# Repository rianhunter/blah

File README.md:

# [CXADC][cxadc] clock generator and audio ADC

A project to synchronously clock two (or more) [CXADC][cxadc] PCIe cards and an extra audio ADC from an external clock generator, for [VHS-Decode][vhs-decode] setups.
This enables sync capturing of the two RF streams (RF Video and RF HiFi audio from a VHS), in addition to a stereo audio stream (linear VHS audio).

The above picture shows the mainboard, which you would typically mount inside your capture PC, along side the 2 CXADC cards.
The below diagram shows how a typical VHS capture is setup using the clock generator + audio ADC (this project).

The project consists of 3 main components:
- A PCB adapter that is installed per PCIe card.
  It contains only a couple of passive components per [cx25800-11z data sheet][google-cx25800-datasheet].
- The main PCB that combines a [Raspberry Pi Pico][pi-pico], with an [Adafruit Si5351A Clock Generator Breakout Board][si5351-adafruit], and a [PCM1802 board][pcm1802-product].
- The firmware for the [Raspberry Pi Pico][pi-pico], that implements a USB sound card and also controls the [Si5351A][si5351-adafruit] clock generator.
  The firmware is available pre-build and can be flashed to the [Raspberry Pi Pico][pi-pico] without additional tools.

## Why you would need this

To capture VHS conveniently and then decode it with the amazing [VHS-Decode][vhs-decode], you need two [CXADC][cxadc] PCIe cards and an additional audio ADC.
One [CXADC][cxadc] card will capture the RF video stream at usually 20MSPS 10bit.
The other [CXADC][cxadc] card will capture RF HiFi audio at usually 10MSPS 8bit.
The additional audio ADC captures the linear audio track from the VHS.
So you have 3 independent pieces of hardware that each captures a part of the VHS tapes content.

Each of the 3 pieces has its own quartz oscillator, to drive its logic.
[CXADC][cxadc] PCIe cards usually come with a 28.6MHz quartz, that is commonly replaced with a 40MHz one for better performance.
The additional linear audio stream could be captured with an additional USB audio interface, which of course has its own quartz.

As every real device, quartzes have tolerances, resulting in frequency errors.
E.g. a 40MHz quartz might actually be 40.000005MHz or 39.999995MHz.
This error is due to manufacturing tolerance and basically random.
So each of the 3 quartzes will be slightly different, and you can't really know by how much.
If you just capture from one of these sources, then this tiny error does not matter.
But if you capture 3 streams that all come from the same source, a VHS tape, then it does!

So lets say that one [CXADC][cxadc] card is slightly faster than the other, because its quartz runs a bit faster than the others.
When you've finished your capture from both cards, one file will contain slightly more samples than came from the other stream.
This means the signal / information in both files is actually not aligned with each other any more, like it used to be on the VHS tape.
To align them again, you have to do (manual) post processing to find out how much they differ, and then *resample* one of them to fit the other.
The same goes for the linear audio as well, there may now be slightly more or less samples in your recorded wav file than expected.

This project solves all of this by replacing the quartz crystals on [CXADC][cxadc] PCIe cards with the output from a clock generator.
The clock generator produces the clocks for both cards from a single source (also a quartz).
This single source of course has a slight error, but as both [CXADC][cxadc] cards are now fed from the *same* source, both are now always in sync!
To also cover the linear audio capturing / recording, the project includes a [PCM1802 ADC][pcm1802-product].
This extra audio ADC is also synchronously clocked from the same clock generator, so it is also always in sync to the two [CXADC][cxadc] cards.

As an added bonus, the clock generator is programmable, so the output sample rates for the [CXADC][cxadc] cards can be changed!
This can be configured during system runtime, via the same USB audio interface that also streams the [PCM1802 ADC][pcm1802-product] samples.
And as one more feature, it also contains an additional digital input, that can be connected to the head switch signal of your VHS player.
This signal will be recorded along side the linear audio, enabling even more automation to sync up all those streams.

The above shows a 3ch recording as captured from the clock generator, a sine wave on the left, silence on the right, and a head-switch signal on the 3rd channel.
Read on to get all the details and find out how to build one yourself.

## Building one yourself

The build and installation guide can be found [over here][build-guide].
Have a look in the [mechanical section too](mechanical) for some (optional) 3D printable parts.
And once you built it, check out the [scripts][scripts] folder which holds some useful tools an examples around using this project.

## System overview and architecture

So you want to contribute, or just understand how it all works, then read on!
Lets start with a logical block diagram of the system.

The brain of the system is a [Raspberry Pi Pico][pi-pico] that implements a [USB UAC][wiki-usb-uac] device (aka a usb sound card).
The [USB UAC][wiki-usb-uac] device can be used to stream the captured samples from the [PCM1802][pcm1802-product] as a regular sound source.
In addition to audio streaming it also offers control over the sample rates for the ADC and [CXADC][cxadc] cards.
[USB UAC][wiki-usb-uac] is supported by all major OS and should work without the need for any additional drivers.
Here's the output from `arecord` when the clock gen is plugged in:

NOTE the following talks a lot about the implementation as a [USB UAC 2.0 audio device][wiki-usb-uac].
The backgrounds and details can be found in the "Device Class Specification Adopters Agreement", aka. [the USB audio specification][usb-auc-20-spec].
So you may want to read through the first 3 chapters to get the full background.

The [USB UAC device][wiki-usb-uac] offers two sample rates for the [PCM1802][pcm1802-product], that can be switched via a UAC clock source.
This is [done automatically by your OS / sound system][multi-samplerate] so just select your desired capture rate with your sound recorder of choice.
To enable clock frequency switching on the [CXADC][cxadc] cards however a UAC clock source would most likely not work.
ALSA and other sound systems will configure UAC clock sources only when capturing from a linked stream.
The [CXADC][cxadc] cards however are not linked to any audio data you could stream from the UAC device.
So instead the various clock rates are implemented as (fake) internal audio streams that can be switched with a UAC switch control.
Internal audio streams are per UAC specification not available to the outside and as such should not trouble OS sound systems for not offering a way to stream their data.
Every clock frequency is represented as one (virtual/internal/fake) input stream, and each of the two [Si5351A][si5351-adafruit] clock output is represented as one (virtual/internal/fake) output.
So to the OS / sound system this looks like a switch matrix of various audio stream sources, switched onto two outputs.
This will generate entries in the usual mixer widgets / apps, that let you control your general sound card settings.
But instead of switching actual audio streams, the UAC selector unit of course switches clock frequencies for the attached [CXADC][cxadc] cards.

This is all a bit abstract, so here's how those switches are displayed in `alsamixer` (you can switch the rates simply using the arrow keys on your keyboard):

And here's how `amixer` can be used to script switching the clock rate on output 0:

To help with readability and to more closely match the USB UAC implementation, the above system diagram shows the clock system to have all frequencies generated at all times, and then switched per output.
In reality the [Si5351A][si5351-adafruit] features only one "Multi Synth" per clock output. 
So the switches are not switching clock paths but rather configurations of "Multi Synths".

The setup offers a couple of options for both the [PCM1802][pcm1802-product] audio ADC and the [CXADC][cxadc], but not all of them are of equal quality.
Inside the [Si5351A][si5351-adafruit] clock generator, two [PLLs][pll-wiki] are used to generate intermediate frequencies.
Those intermediate clock are then further divided to get the desired clock frequencies at the 3 outputs.

PLL A is running in integer mode, which means only whole number multipliers are used, resulting in no added [jitter][jitter-wiki].
Further more the subsequent "multi synth" dividers are also in integer mode, again resulting in no added [jitter][jitter-wiki].
But this limits the clock outputs options to only frequencies that can be produced by one multiplication and one division with only whole numbers.
Based on the 25 MHz source that is included on the [Si5351A][si5351-adafruit] board, this enables CXADC *sampling clocks of 20 MHz, 40 MHz and 50 MHz*.
The [PCM1802][pcm1802-product] needs a clock of 256 times the frequency of the desired output audio sampling rate.
The PLL A path generates a 12 MHz output which results in an exact (without rounding error) *46875 Hz / 46.875 kHz* sample rate for the audio stream.
This uncommon rate does not degrade the performance of the [PCM1802][pcm1802-product] ADC and offers analog bandwidth that is above CD quality.
Using common tools (sox or ffmpeg) the captured pcm data can be fully automatically resampled to the more common 48 kHz or 44.1 kHz in an offline processing step.

PLL B is running is running in fractional mode, yielding an increased clock [jitter][jitter-wiki].
Together with fractional configuration in the subsequent "multi synth" dividers, two more clock rates are possible.
The [CXADC][cxadc] can be clocked with the same frequency as the stock crystal 28.636360 MHz.
And the [PCM1802][pcm1802-product] can be clocked with a 12.288 MHz, giving the more common 48 kHz as output sample rate.
In ADCs [the higher the clock jitter the worse the sampling quality][jitter-paper] will be.
So you should avoid these sampling rates if you can and only use the ones from the integer mode PLL A.

## Debugging, global status and the mysterious mute switch

As this project is put together from various components (main board, sub boards, etc.), quite a few things can go wrong.
The firmware will output debugging information over the UART0 on the Pi Pico (GPIO0 / Pin1).
So hooking up a serial adapter is a good idea when working on the code (see also [dbg.h](firmware/src/dbg.h)).
However when just assembling the project, users may not have the option to do that, so a more practical way of obtaining debugging info is needed.
This does not have to be all the debug output that happens everywhere, but it should be enough to find common problems.

[USB UAC][wiki-usb-uac] unfortunately does not give many options to achieve that.
There is a "Memory Requests" (chapter [5.2.7.1][usb-auc-20-spec]) which would be perfect, but there is no common user space tool available.
User space support with regular tools is important as this is what users will have, and what the [collect-info.sh][scripts] script can use.
So instead of writing a custom tool, we just re-use the audio data that streams from the ADC.
But that can't be happening all the time, and the ADCs might even be non-working, so there must be a way to switch this on and off.
This can be done with a simple mute switch on a feature unit.
If muted debug info will be output, if un-muted (the default after boot), then actual ADC data will be streamed.

The above shows how `alsamixer` displays the on / un-muted state (can be toggled with the *space* bar).

Now what is inside the debug info, you may ask?
Well there is a global status object [global_status.h](firmware/src/global_status.h) that is updated at the relevant places in the code.
It contains flags that indicate errors, and some other values of interest.
This object is dumped in the audio data and streamed to the host.
In other words, to get the debug data, just mute the stream and record a short piece of "audio" with `arecord`.

Have a look at the troubleshooting section of the [build guide][build-guide] if you need help getting the system running.

## Versioning

The firmware / software part is using [Semantic Versioning][semver], referring to the USB device interface.
Tags on this repository will carry the firmware / software version.

The PCBs are versioned with a letter revision.
These revisions do not imply any compatibility, and are solely used to differentiate one revision from another.
PCB revision overview:
- VT610ex clock generator adapter
  - Revision A - never released
  - Revision B - first public release
  - Revision C - some updates to the silkscreen and moved one via to get PcbWay support, otherwise identical to Revision C
  - Revision D - update connector footprint to better fit SMA edge connector and still be compatibile with pin header edge mount
- Clock generator main board
  - Revision A - first public release
  - Revision B - fixes the IO VDD for Si5351, which should be 3.3V, Rev A erroneously had it at VSys
  - Revision C - fixes the 3.3V from PCM1802 being driven by Pi Pico, instead this is an output and should be left open

## Changelog

See [CHANGELOG.md](CHANGELOG.md).

## Releases

See [releases](https://gitlab.com/wolfre/cxadc-clock-generator-audio-adc/-/releases) for PCB gerbers and firmware images ready to flash.

# License

The content of this repository is under various licenses.
The PCB parts are generally under *Creative Commons Attribution-ShareAlike 4.0*, but contains external sources (with compatible licenses).
The source code is mostly under 3-Clause BSD, but contains external sources with compatible licenses mixed in.
Source files carry an [SPDX][spdx] header to indentify.
For details see the individual *LICENSE\** files in the respective folders they apply to, firmware zip packages contain a copy of all the applicable license files.

[cxadc]: https://github.com/happycube/cxadc-linux3/
[pi-pico]: https://www.raspberrypi.com/products/raspberry-pi-pico/
[si5351-adafruit]: https://www.adafruit.com/product/2045
[pcm1802-product]: https://www.ti.com/product/PCM1802
[google-cx25800-datasheet]: https://www.google.com/search?q=DSH-201233A
[semver]: https://semver.org/
[wiki-usb-uac]: https://en.wikipedia.org/wiki/USB#Audio_streaming
[multi-samplerate]: https://stackoverflow.com/questions/41702932/usb-audio-class-2-0-how-to-support-multiple-bit-rates-sample-rates
[pll-wiki]: https://en.wikipedia.org/wiki/Phase-locked_loop
[jitter-wiki]: https://en.wikipedia.org/wiki/Jitter
[jitter-paper]: https://www.analog.com/media/en/reference-design-documentation/design-notes/dn1013f.pdf
[spdx]: https://spdx.dev/
[vhs-decode]: https://github.com/oyvindln/vhs-decode
[usb-auc-20-spec]: https://www.usb.org/sites/default/files/Audio2.0_final.zip
[scripts]: scripts
[build-guide]: build-guide/README.md

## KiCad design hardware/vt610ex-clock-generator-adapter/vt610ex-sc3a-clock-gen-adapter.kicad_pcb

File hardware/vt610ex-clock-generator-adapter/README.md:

# VT610ex clock generator insert

A PCB adapter to replace the quarz oscillator on a VT610ex PICe capture card.

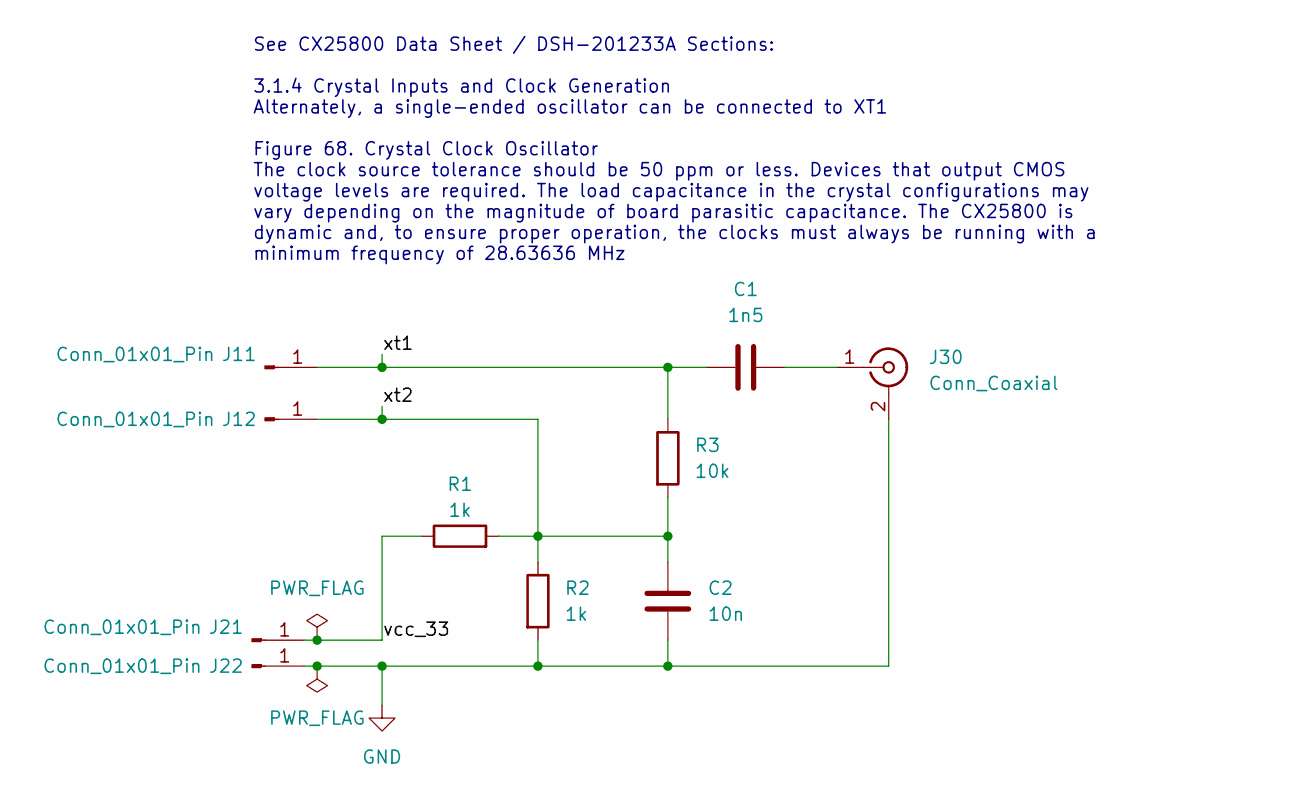
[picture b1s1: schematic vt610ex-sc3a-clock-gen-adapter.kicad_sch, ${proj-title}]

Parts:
C1: 1n5; C_0805_2012Metric_Pad1.18x1.45mm_HandSolder
C2: 10n; C_0805_2012Metric_Pad1.18x1.45mm_HandSolder
J11, J12, J21, J22: Conn_01x01_Pin; TestPoint_Pad_D2.0mm
J30: Conn_Coaxial; SMA_Samtec_SMA-J-P-X-ST-EM1_EdgeMount
R1, R2: 1k; R_0805_2012Metric_Pad1.20x1.40mm_HandSolder
R3: 10k; R_0805_2012Metric_Pad1.20x1.40mm_HandSolder

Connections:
/vcc_33: J21.1, R1.1
/xt1: C1.2, J11.1, R3.1
/xt2: C2.1, J12.1, R1.2, R2.1, R3.2
GND: C2.2, J22.1, J30.2 (Ext), R2.2
unnamed: C1.1, J30.1 (In)

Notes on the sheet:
See CX25800 Data Sheet / DSH-201233A Sections: 3.1.4 Crystal Inputs and Clock Generation Alternately, a single-ended oscillator can be connected to XT1 Figure 68. Crystal Clock Oscillator The clock source tolerance should be 50 ppm or less. Devices that output CMOS voltage levels are required. The 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

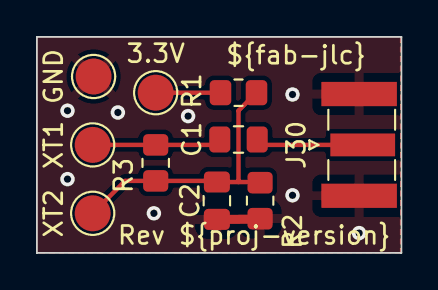
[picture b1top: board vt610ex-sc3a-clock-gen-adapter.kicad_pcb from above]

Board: 2 copper layers, 20.2 x 12.0 mm, 10 parts (0 on the bottom side), 5 nets.

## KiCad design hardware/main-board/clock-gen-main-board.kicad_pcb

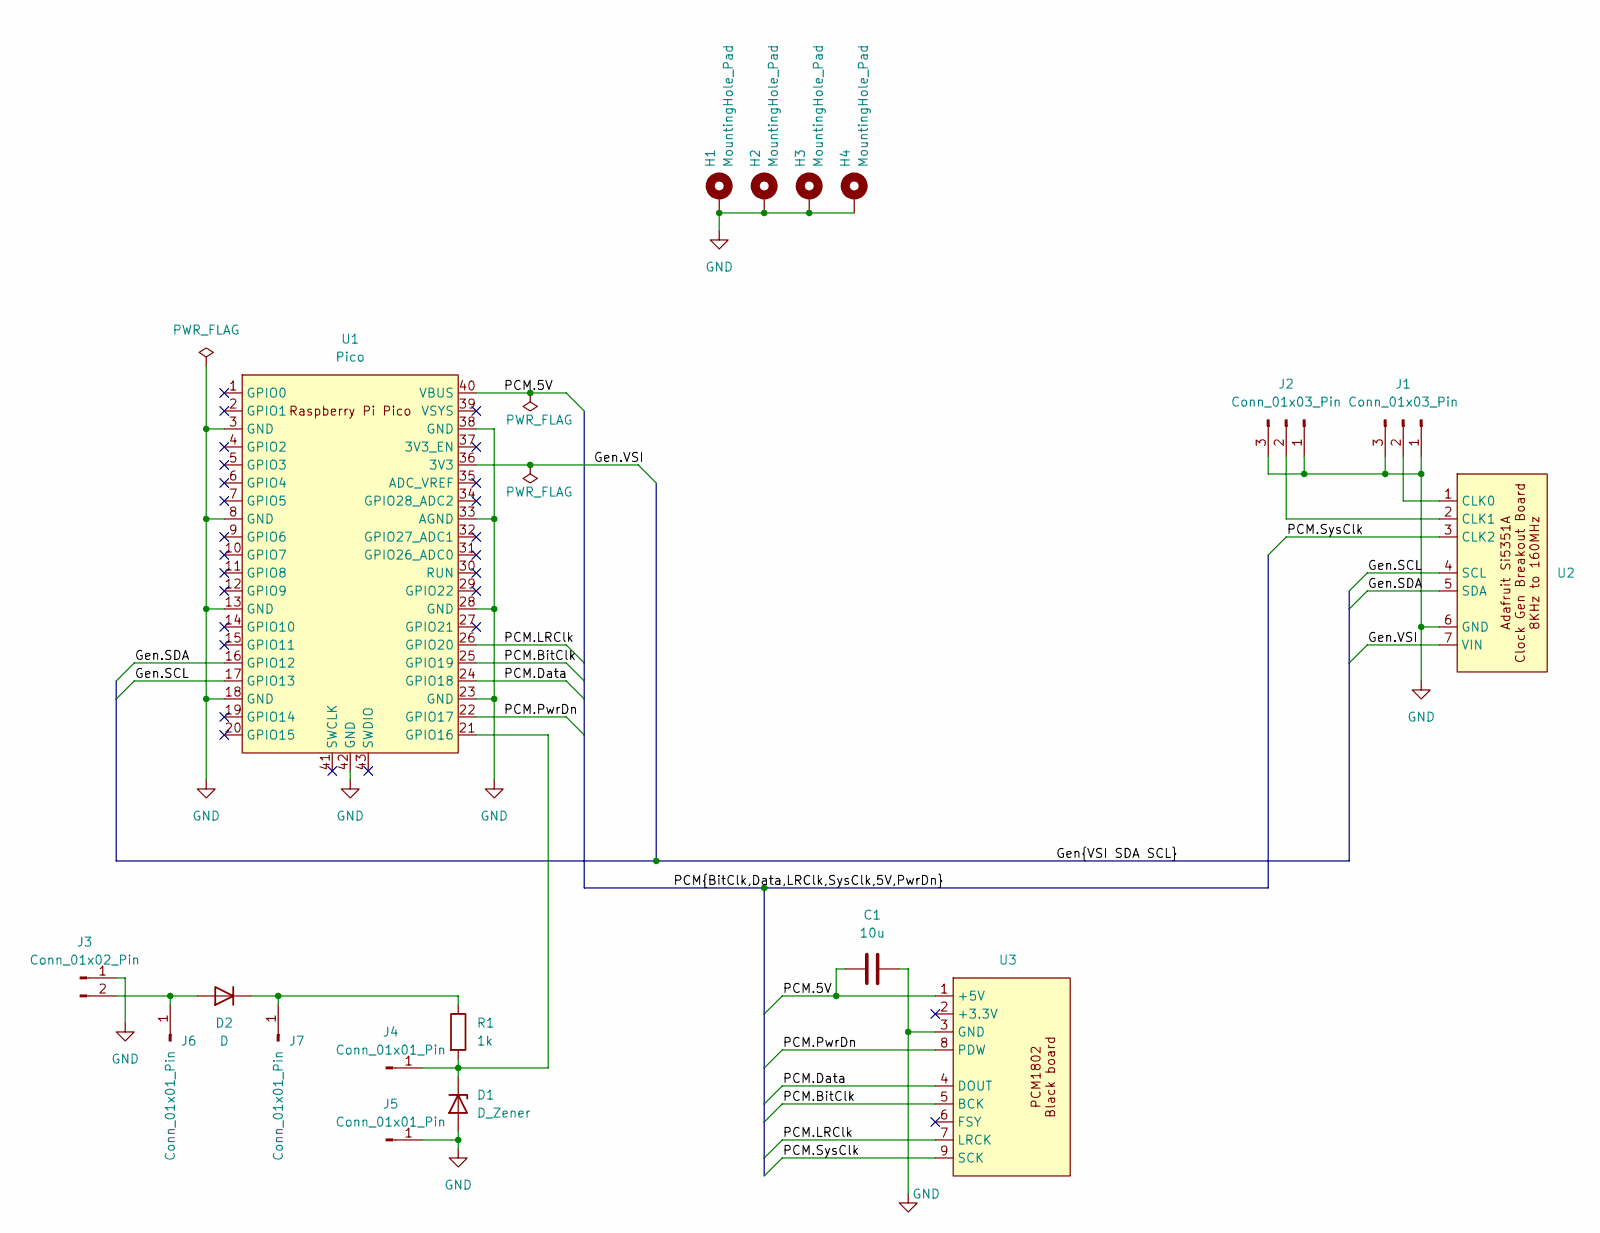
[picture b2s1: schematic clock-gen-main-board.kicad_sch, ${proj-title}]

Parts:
C1: 10u; C_0805_2012Metric_Pad1.18x1.45mm_HandSolder
D1: D_Zener; D_SOD-123
D2: D; D_SOD-123
H1, H2, H3, H4: MountingHole_Pad; MountingHole_3.2mm_M3_ISO14580_Pad
J1, J2: Conn_01x03_Pin; PinHeader_1x03_P2.54mm_Vertical
J3: Conn_01x02_Pin; PinHeader_1x02_P2.54mm_Vertical
J4, J5, J6, J7: Conn_01x01_Pin; PinHeader_1x01_P2.54mm_Vertical
R1: 1k; R_0805_2012Metric_Pad1.20x1.40mm_HandSolder
U1: Pico; RPi_Pico_SMD_TH
U2: Adafruit_Si5351A_Breakout_Board
U3: black-pcm1802-board

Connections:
/Gen.SCL: U1.17 (GPIO13), U2.4 (SCL)
/Gen.SDA: U1.16 (GPIO12), U2.5 (SDA)
/Gen.VSI: U1.36 (3V3), U2.7 (VIN)
/PCM.5V: C1.1, U1.40 (VBUS), U3.1 (+5V)
/PCM.BitClk: U1.25 (GPIO19), U3.5 (BCK)
/PCM.Data: U1.24 (GPIO18), U3.4 (DOUT)
/PCM.LRClk: U1.26 (GPIO20), U3.7 (LRCK)
/PCM.PwrDn: U1.22 (GPIO17), U3.8 (PDW)
/PCM.SysClk: U2.3 (CLK2), U3.9 (SCK)
GND: C1.2, D1.2 (A), H1.1, H2.1, H3.1, H4.1, J1.1, J1.3, J2.1, J2.3, J3.1, J5.1, U1.3 (GND), U1.8 (GND), U1.13 (GND), U1.18 (GND), U1.23 (GND), U1.28 (GND), U1.33 (AGND), U1.38 (GND), U1.42 (GND), U2.6 (GND), U3.3 (GND)
unnamed: D1.1 (K), J4.1, R1.2, U1.21 (GPIO16)
unnamed: D2.2 (A), J3.2, J6.1
unnamed: D2.1 (K), J7.1, R1.1
unnamed: J1.2, U2.1 (CLK0)
unnamed: J2.2, U2.2 (CLK1)

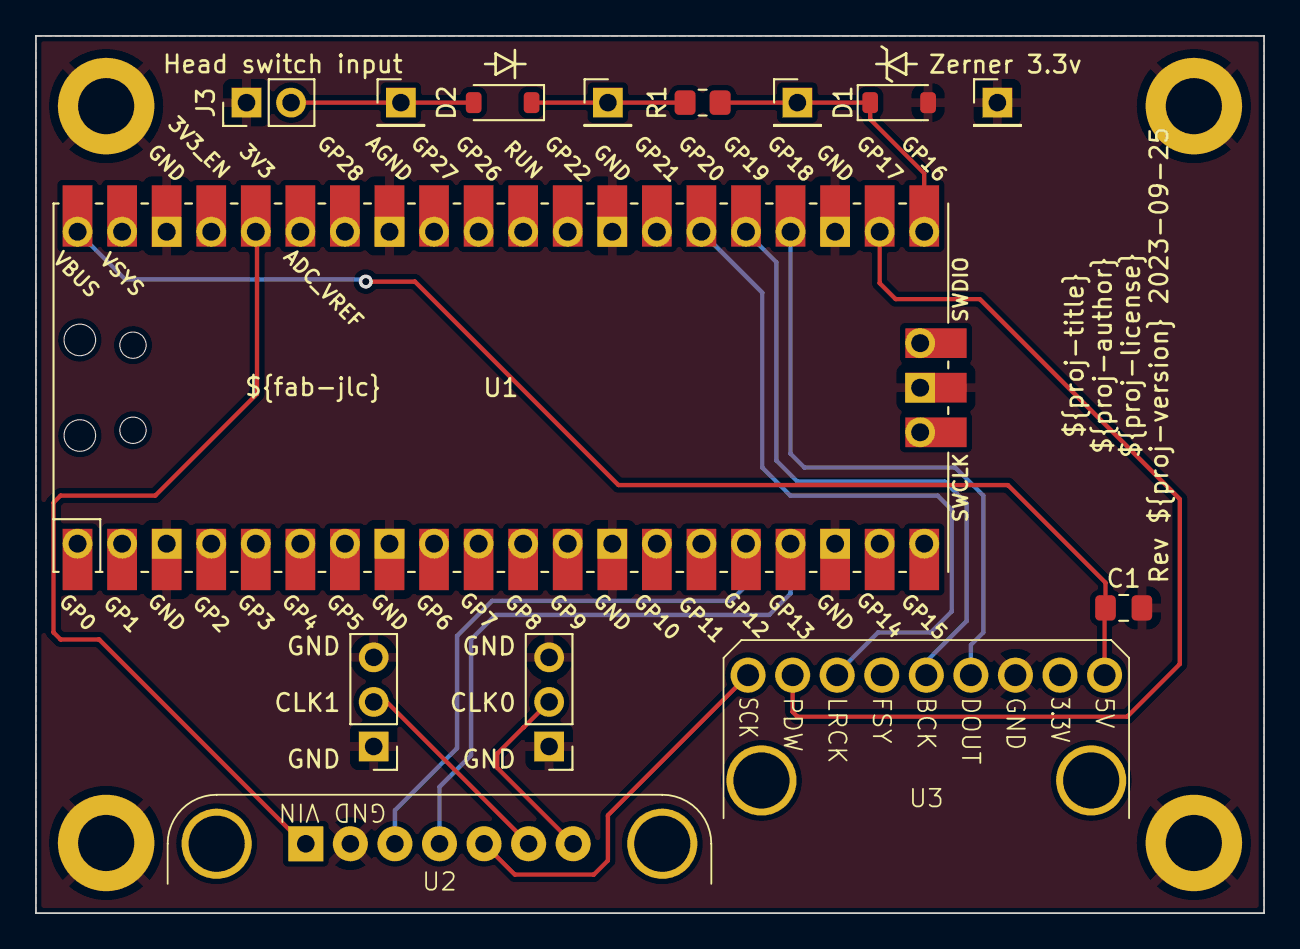
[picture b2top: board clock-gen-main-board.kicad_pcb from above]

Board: 2 copper layers, 70.0 x 50.0 mm, 18 parts (0 on the bottom side), 15 nets.

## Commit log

2023-09-10 Resolve "Add vt610ex clock gen adapter"
2023-09-11 Resolve "Add main board"
2023-09-16 Resolve "Extend mainboard with audio ADC"
2023-09-16 Resolve "generate fab outputs for pcb production"
2023-09-17 Resolve "Create firmware hello world"
2023-09-22 Resolve "implement clock gen startup to fixed 40Mhz"
2023-09-23 fix iovdd
    - create new gerbers
    - create new render
    - update readme
    - update changelog
2023-09-23 more work Sa 23. Sep 10:18:38 CEST 2023
2023-09-24 Resolve "update changelog for v0.1.0"
2023-09-25 Resolve "PCM1802 board 3.3V pin is driven instead of open"
2023-09-26 Resolve "implement basic stub UAC device"
2023-10-01 Resolve "build 3d printable box enclosure"
2023-10-02 Resolve "populate pcbs and write build guide"
2023-10-02 Resolve "update changelog for v0.2.0"
2023-10-02 Resolve "add lower clock frequencies best fit for vhs rf hi-fi audio sampling"
2023-10-03 Resolve "Remove 5MHz and 10MHz options or make them optional"
2023-10-03 Resolve "implement i2s pio and stream pcm1802 adc data"
2023-10-06 Resolve "extend enclosure with retainer"
2023-10-06 Resolve "add rca jack pc bracket"
2023-10-08 Resolve "create a demo script for a two card capture + linear audio"
2023-10-08 Resolve "some doc improvements"
2023-11-25 Draft: Resolve "Create a info collect script to help trouble shoot"
2023-11-25 Resolve "Add troubleshooting to build guide"
2023-11-25 Resolve "PCBway Compatible Gerbers"
2023-11-26 Resolve "Extend build guide to explain SMA connectors for clock lines"
2023-11-26 Resolve "Fix overview diagram to show 40MSps 8Bit on both HiFi and Video RF to be aligned with capture script"
2023-11-26 Resolve "Extend firmware to offer some debugging options for sub board problems"
2023-12-03 Resolve "A few improvements to the trouble shooting guide"

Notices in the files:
parts and their libraries:
proj-license: CC BY-SA 4.0
